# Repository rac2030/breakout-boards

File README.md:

# breakout-boards
Various breakoutboards for electronic components I play with

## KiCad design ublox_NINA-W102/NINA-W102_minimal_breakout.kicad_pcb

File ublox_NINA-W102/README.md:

# ublox NINA-W102 breakout for breadboard prototyping
Project page with more information and background: http://rac.su/ninab

Hackaday Project entry: https://hackaday.io/project/151749-ublox-nina-w102-minimal-breakout

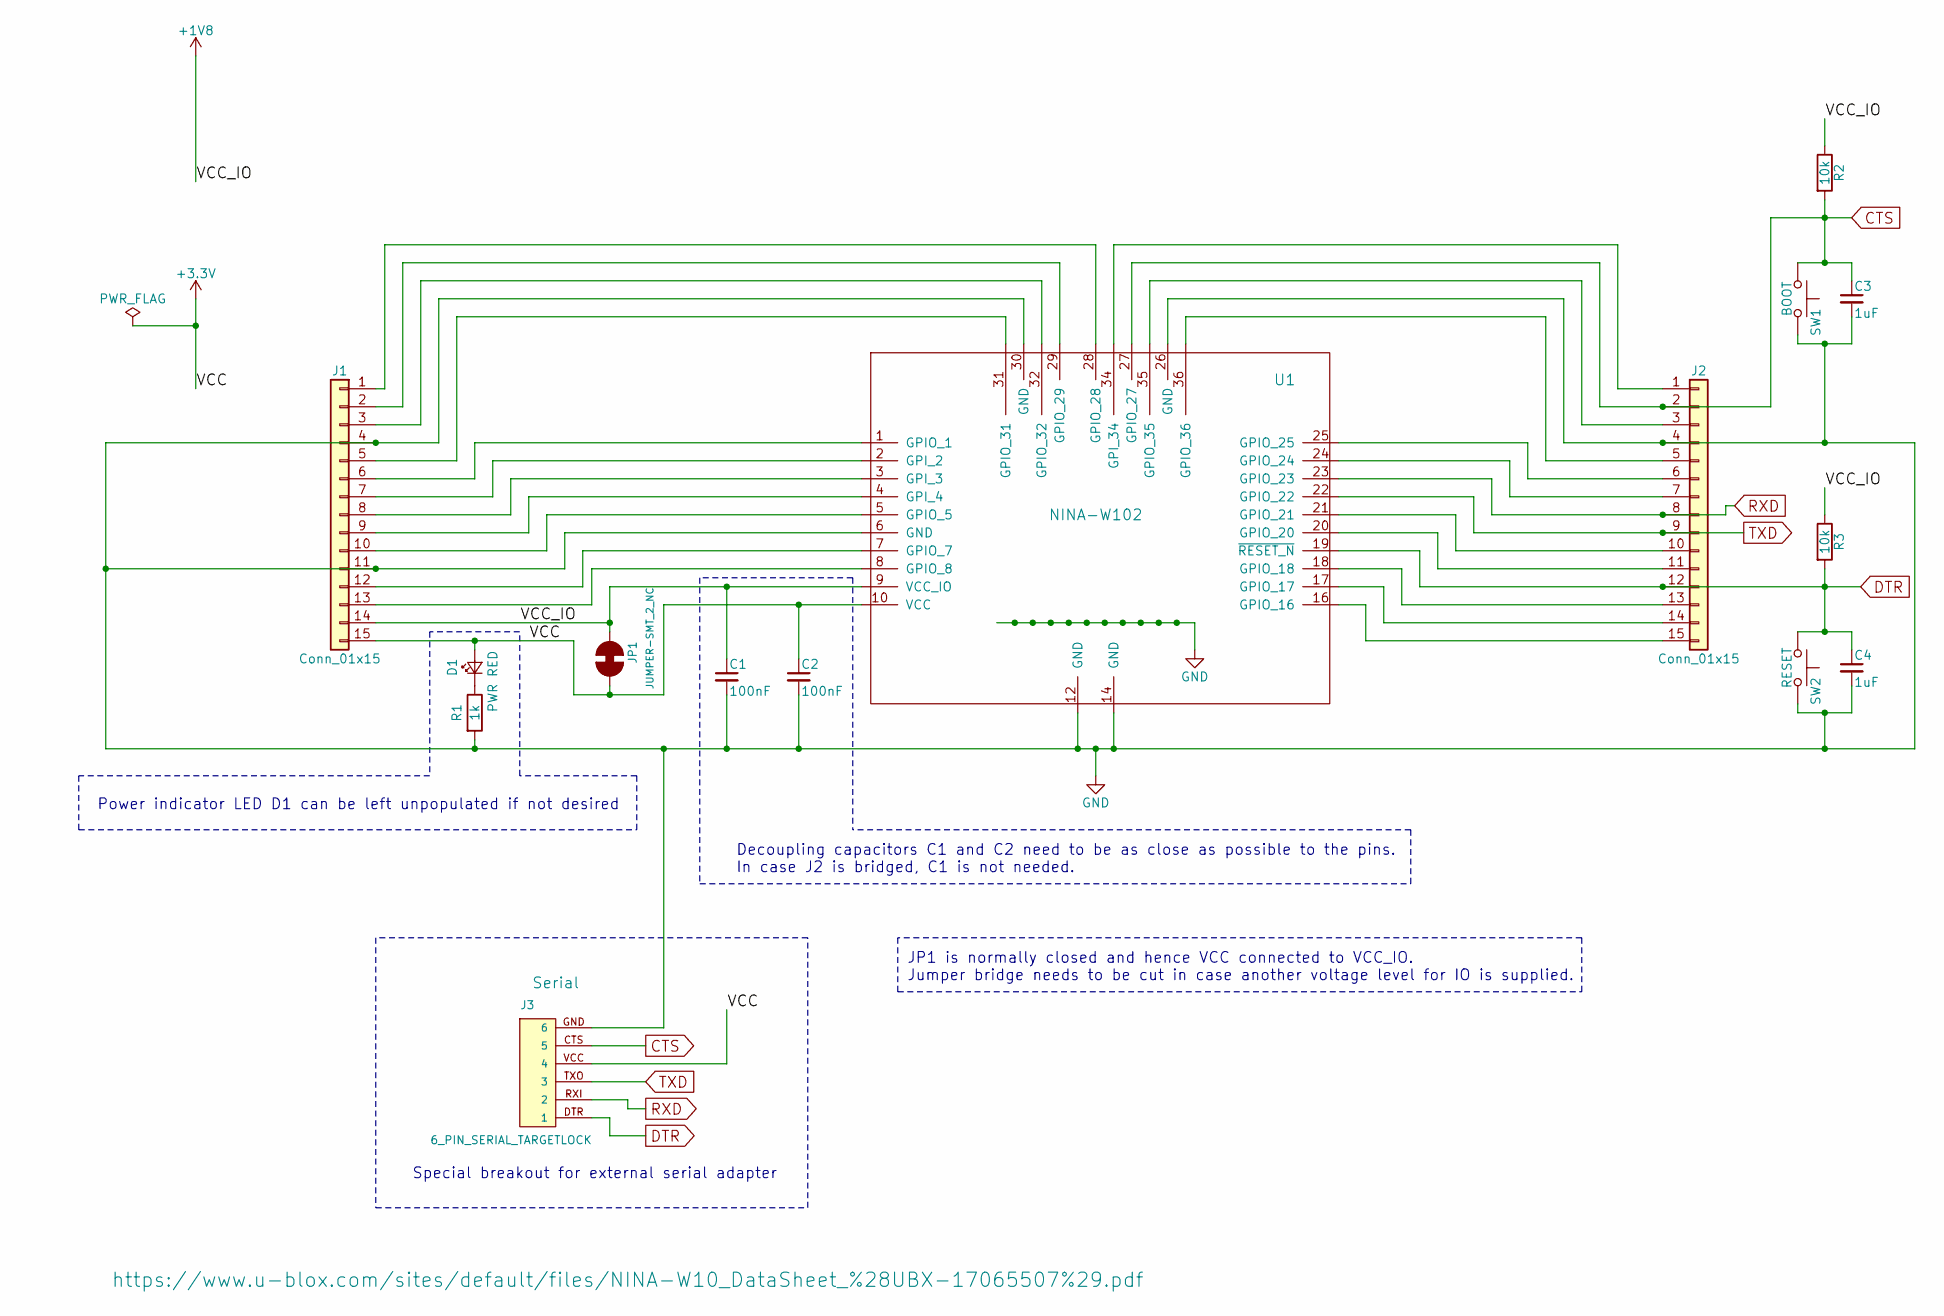
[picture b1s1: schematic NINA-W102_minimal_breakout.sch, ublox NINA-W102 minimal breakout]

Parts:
C1, C2: 100nF; C_1206_HandSoldering
C3, C4: 1uF; C_1206_HandSoldering
D1: PWR RED; LED_1206_HandSoldering
J1, J2: Conn_01x15; 1X15_LOCK
J3: 6_PIN_SERIAL_TARGETLOCK; 6_PIN_SERIAL_TARGET_SIDE_W_SILK
JP1: JUMPER-SMT_2_NC; SMT-JUMPER_2_NC_TRACE_SILK
R1: 1k; R_1206_HandSoldering
R2, R3: 10k; R_1206_HandSoldering
SW1: BOOT; TACTILE_SWITCH_SMD_6.0X6.0MM
SW2: RESET; TACTILE_SWITCH_SMD_6.0X6.0MM
U1: NINA-W102

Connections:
+1V8: C1.1, J1.14, JP1.1, R2.1, R3.1, U1.9 (VCC_IO)
+3V3: C2.1, D1.2 (A), J1.15, J3.VCC (4), JP1.2, U1.10 (VCC)
CTS: C3.1, J2.2, J3.CTS (5), R2.2, SW1.1, U1.27 (GPIO_27)
DTR: C4.1, J2.12, J3.DTR (1), R3.2, SW2.1, U1.19 (~RESET_N)
GND: C1.2, C2.2, C3.2, C4.2, J1.4, J1.11, J2.4, J3.GND (6), R1.2, SW1.2, SW2.2, U1.6 (GND), U1.12 (GND), U1.14 (GND), U1.26 (GND), U1.30 (GND), U1.37 (GND), U1.38 (GND), U1.39 (GND), U1.40 (GND), U1.41 (GND), U1.42 (GND), U1.43 (GND), U1.44 (GND), U1.45 (GND), U1.46 (GND), U1.47 (GND), U1.48 (GND)
unnamed: D1.1 (K), R1.1
unnamed: J1.1, U1.28 (GPIO_28)
unnamed: J1.2, U1.29 (GPIO_29)
unnamed: J1.3, U1.32 (GPIO_32)
unnamed: J1.5, U1.31 (GPIO_31)
unnamed: J1.6, U1.1 (GPIO_1)
unnamed: J1.7, U1.2 (GPI_2)
unnamed: J1.8, U1.3 (GPI_3)
unnamed: J1.9, U1.4 (GPI_4)
unnamed: J1.10, U1.5 (GPIO_5)
unnamed: J1.12, U1.7 (GPIO_7)
unnamed: J1.13, U1.8 (GPIO_8)
unnamed: J2.1, U1.34 (GPI_34)
unnamed: J2.3, U1.35 (GPIO_35)
unnamed: J2.5, U1.36 (GPIO_36)
unnamed: J2.6, U1.25 (GPIO_25)
unnamed: J2.7, U1.24 (GPIO_24)
unnamed: J2.10, U1.21 (GPIO_21)
unnamed: J2.11, U1.20 (GPIO_20)
unnamed: J2.13, U1.18 (GPIO_18)
unnamed: J2.14, U1.17 (GPIO_17)
unnamed: J2.15, U1.16 (GPIO_16)
RXD: J2.8, J3.RXI (2), U1.23 (GPIO_23)
TXD: J2.9, J3.TXO (3), U1.22 (GPIO_22)

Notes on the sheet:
Decoupling capacitors C1 and C2 need to be as close as possible to the pins. In case J2 is bridged, C1 is not needed.
Power indicator LED D1 can be left unpopulated if not desired
Special breakout for external serial adapter
JP1 is normally closed and hence VCC connected to VCC_IO. Jumper bridge needs to be cut in case another voltage level for IO is supplied.

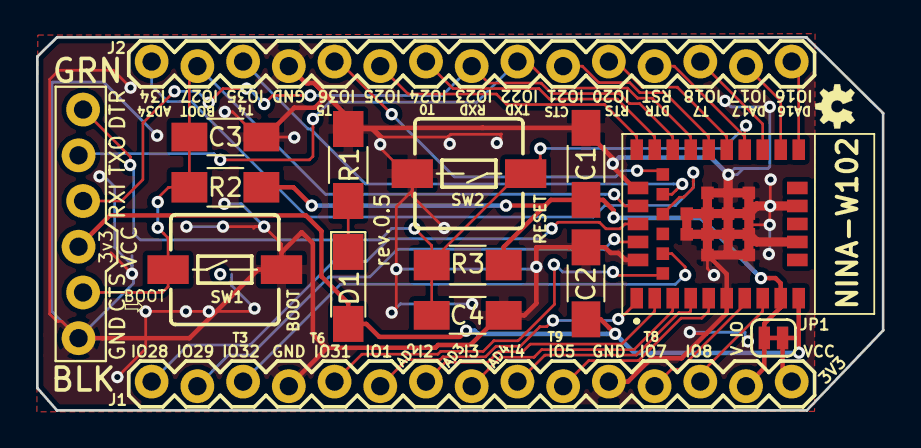
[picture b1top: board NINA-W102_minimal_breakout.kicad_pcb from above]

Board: 2 copper layers, 47.0 x 20.7 mm, 16 parts (1 on the bottom side), 29 nets.

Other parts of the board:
MakeZurich-15x11-silk: G***; MakeZurich-15x11-silk

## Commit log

2018-04-13 Added FPC breakout for sensirion samples
2018-04-13 added 3D rendering
2018-04-17 Added printout for rev.0.3
2018-04-17 Added first version schematic
2018-04-18 Fixed CTS PIN and added fpx sample mage from sensirion
2018-04-19 initial layout done without wiring
2018-04-19 First routing done
2018-04-19 Cleanup of leftover files
2018-04-19 First try with groundplane
2018-04-21 Rerouting and thickening power tracks to 10mils, integrating some of the feedback from Michael
2018-04-21 Added some ground pad vias and corrected placement of problematic vias as feedback from Michael Ammann
2018-04-21 Added rendering images of PCB rev.0.3
2018-04-21 Added README with renderings
2018-04-21 Corrected solder mask on Jumper that the trace will be easy cuttable
2018-04-22 Added revision info on front PCB
2018-04-22 Added some silk labels for pins from datasheet
2018-04-22 Added missing AD pin label
2018-04-22 Added dimensions and updated revision
2018-04-22 Simplified some tracks to look nicer
2018-04-22 Did rerun DRC
2018-04-22 Added some ground vias
2018-04-22 Additions and changes to the labeling
2018-04-22 Added some MakeZurich artwork
2018-04-23 DuckTape approved stamp and track angle corrections and some more ground vias
2018-04-24 Added GND pad and labels for sensirion sample flex PCBs
2018-04-24 Added china I2C layout version for Urs Marti
2018-05-03 Added printouts and BOM
2018-05-03 Added schematic components to local library
2018-05-03 Removed external schematic libraries
2018-05-03 Added footprints to local library and reassigned in schematic
2018-05-05 Adding duck-tape seal option
2018-05-20 Add pinout diagram
2018-05-20 Correct FTDI ring positions
2018-05-20 Fix A7 missing
2018-05-21 Change duck tape silkscreen for licensed one ;)
2018-05-21 Corrected silk and added GDG logo
2018-05-25 Update pinout diagram
2018-05-29 Changed schematics to current PCB revision and added all digikey partnumbers visible in the BOM html output
2018-05-29 save
2018-05-29 Fixed breadboard spacing helper component position
2018-06-21 Added manufacturing output and corrected I2C issue with the badge carrier board
